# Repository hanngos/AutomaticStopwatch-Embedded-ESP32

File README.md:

# Description
The topic of this project is an automatic stopwatch (time measuring device), which aims to be used during a local competition. At the starting line, there is a sensor. Once the competitor has crossed it, the time count begins and continues until the competitor crosses the starting line a second time. Information about the time obtained by the competitor will be presented on the display. The stopwatch can be reset by pressing a button and is powered by an externally connected battery (PowerBank) for easy replacement of a discharged power source. The readiness of the device will be indicated by the LED (green when it is possible to start the race, red when the time is running, and blue when the time is finished but the device is not ready to count again).

It was developed as a project for the Microprocessor and Embedded Systems course at Silesian University of Technology.
# Used Elements
◦ microcontroller - ESP32 DevKit V1
◦ laser beam sensor - A-CZWL
◦ display - Gravity DFR0646-G
◦ 3.3V / 5V logic level converters
◦ 5mm RGB diode
◦ resistors: 10, 33, 62, 2x 2k2 and 10k Ω
◦ 5 mW red laser
◦ Grove cable
◦ USB cable
◦ Power Bank

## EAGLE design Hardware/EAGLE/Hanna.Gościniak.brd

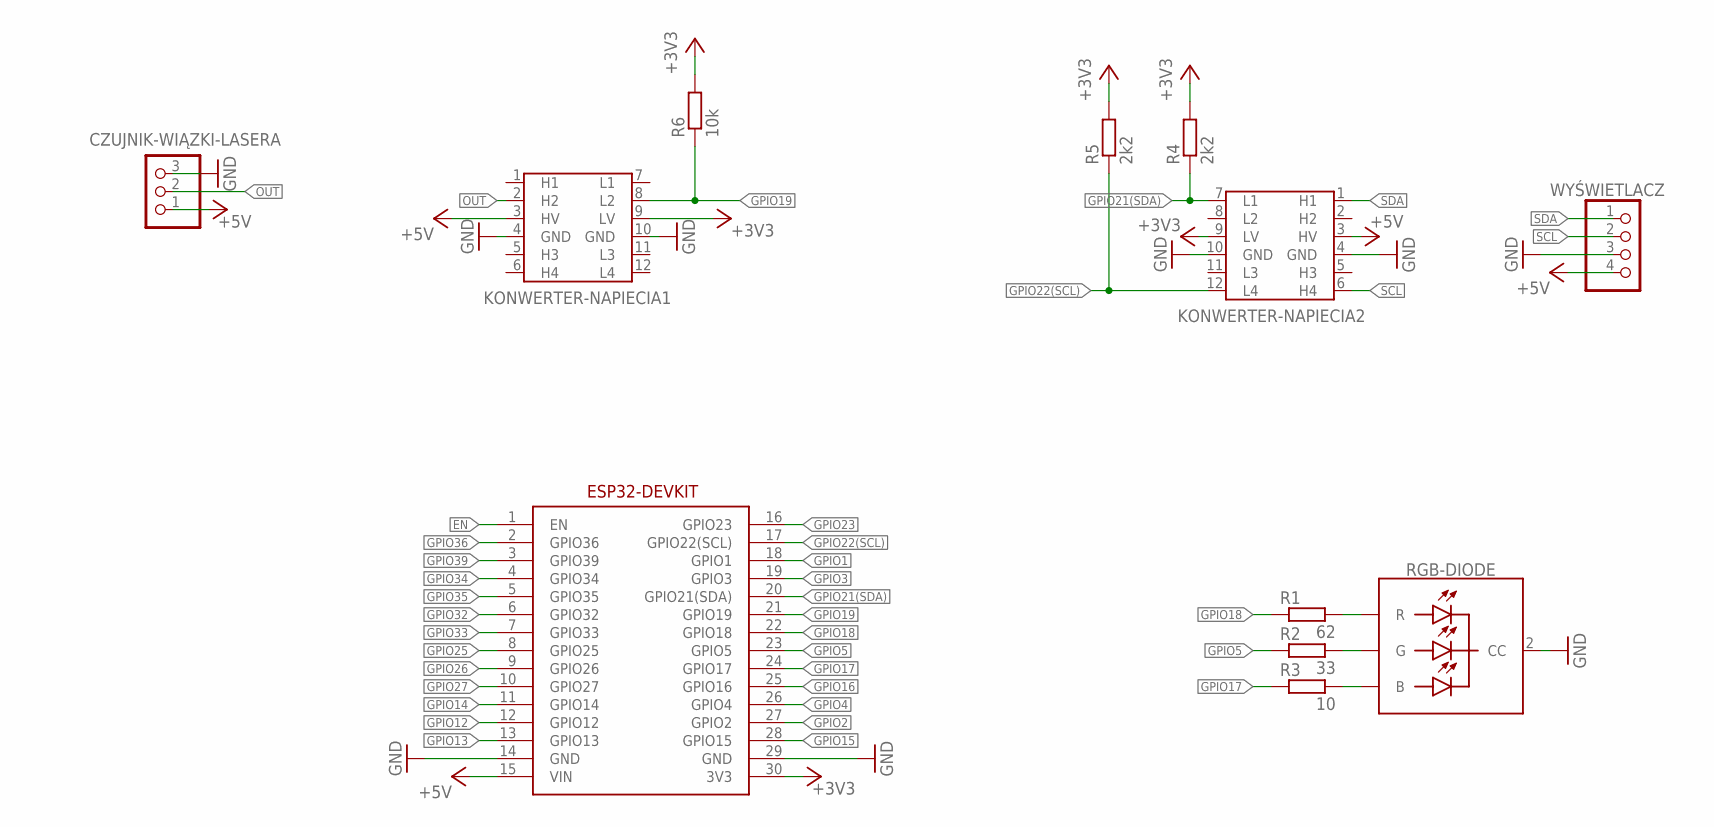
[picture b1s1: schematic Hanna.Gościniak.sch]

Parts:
CZUJNIK-WIĄZKI-LASERA: 1; 1X03
KONWERTER-NAPIECIA1, KONWERTER-NAPIECIA2: KONWERTER-NAPIECIA-3.3/5V
R1: 62; 0207/10
R2: 33; 0207/10
R3: 10; 0207/10
R4, R5: 2k2; 0207/10
R6: 10k; 0207/10
RGB1: RGB-DIODE; RGB
U$1: ESP32-DEVKIT
WYŚWIETLACZ: 1; 1X04

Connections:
+3V3: KONWERTER-NAPIECIA1.9 (LV), KONWERTER-NAPIECIA2.9 (LV), R4.2, R5.2, R6.2, U$1.30 (3V3)
+5V: CZUJNIK-WIĄZKI-LASERA.1, KONWERTER-NAPIECIA1.3 (HV), KONWERTER-NAPIECIA2.3 (HV), U$1.15 (VIN), WYŚWIETLACZ.4
EN: U$1.1 (EN)
GND: CZUJNIK-WIĄZKI-LASERA.3, KONWERTER-NAPIECIA1.4 (GND), KONWERTER-NAPIECIA1.10 (GND), KONWERTER-NAPIECIA2.4 (GND), KONWERTER-NAPIECIA2.10 (GND), RGB1.2 (CC), U$1.14 (GND), U$1.29 (GND), WYŚWIETLACZ.3
GPIO1: U$1.18 (GPIO1)
GPIO2: U$1.27 (GPIO2)
GPIO3: U$1.19 (GPIO3)
GPIO4: U$1.26 (GPIO4)
GPIO5: R2.1, U$1.23 (GPIO5)
GPIO12: U$1.12 (GPIO12)
GPIO13: U$1.13 (GPIO13)
GPIO14: U$1.11 (GPIO14)
GPIO15: U$1.28 (GPIO15)
GPIO16: U$1.25 (GPIO16)
GPIO17: R3.1, U$1.24 (GPIO17)
GPIO18: R1.1, U$1.22 (GPIO18)
GPIO19: KONWERTER-NAPIECIA1.8 (L2), R6.1, U$1.21 (GPIO19)
GPIO21(SDA): KONWERTER-NAPIECIA2.7 (L1), R4.1, U$1.20 (GPIO21(SDA))
GPIO22(SCL): KONWERTER-NAPIECIA2.12 (L4), R5.1, U$1.17 (GPIO22(SCL))
GPIO23: U$1.16 (GPIO23)
GPIO25: U$1.8 (GPIO25)
GPIO26: U$1.9 (GPIO26)
GPIO27: U$1.10 (GPIO27)
GPIO32: U$1.6 (GPIO32)
GPIO33: U$1.7 (GPIO33)
GPIO34: U$1.4 (GPIO34)
GPIO35: U$1.5 (GPIO35)
GPIO36: U$1.2 (GPIO36)
GPIO39: U$1.3 (GPIO39)
unnamed: R1.2, RGB1.1 (R)
unnamed: R2.2, RGB1.3 (G)
unnamed: R3.2, RGB1.4 (B)
OUT: CZUJNIK-WIĄZKI-LASERA.2, KONWERTER-NAPIECIA1.2 (H2)
SCL: KONWERTER-NAPIECIA2.6 (H4), WYŚWIETLACZ.2
SDA: KONWERTER-NAPIECIA2.1 (H1), WYŚWIETLACZ.1

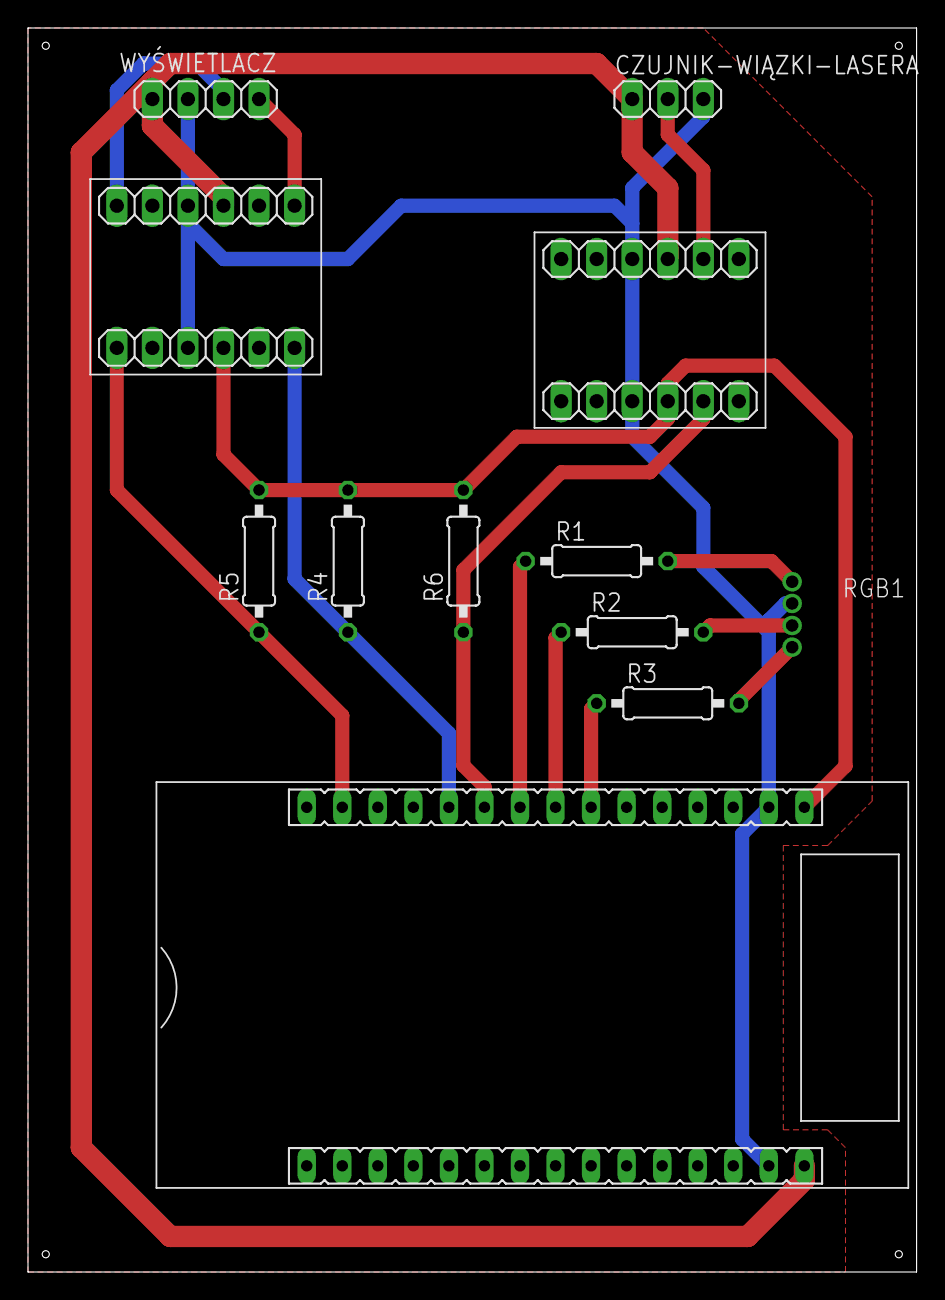
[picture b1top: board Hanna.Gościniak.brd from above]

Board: 2 copper layers, 63.5 x 88.9 mm, 12 parts (0 on the bottom side), 15 nets.

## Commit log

2021-04-12 smiw
